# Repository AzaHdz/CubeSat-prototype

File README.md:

# CubeSat-prototype
Design, Build and test
###### STR: Structure, EPS: Electrical power Subsystem, CDH: Command data and handling, COM: Communications, ADC: Attitude Determination and Control, GCS: Ground Control Station
#### The purpose of this project is to develop the prototype of a CubeSat 1U type satellite, used in real space missions. 
#### 6 subsystems and a Ground control station were designed: EPS, Payload, CDH, COM, ADC, GCS and STR.
#### each subsystem was designed, built and tested
#### Communication protocols used: UART, I2C, Analog, SPI, Zigbee

#### The STR was designed in fusion 360 and built with  a 3d printer.

#### 5 pcb were designed in eagle and later they were manufactured in a chinese company

#### The two microcontrollers were programmed with the Arduino IDE.
#### The GUI was built with Node js and deployed as a web App.

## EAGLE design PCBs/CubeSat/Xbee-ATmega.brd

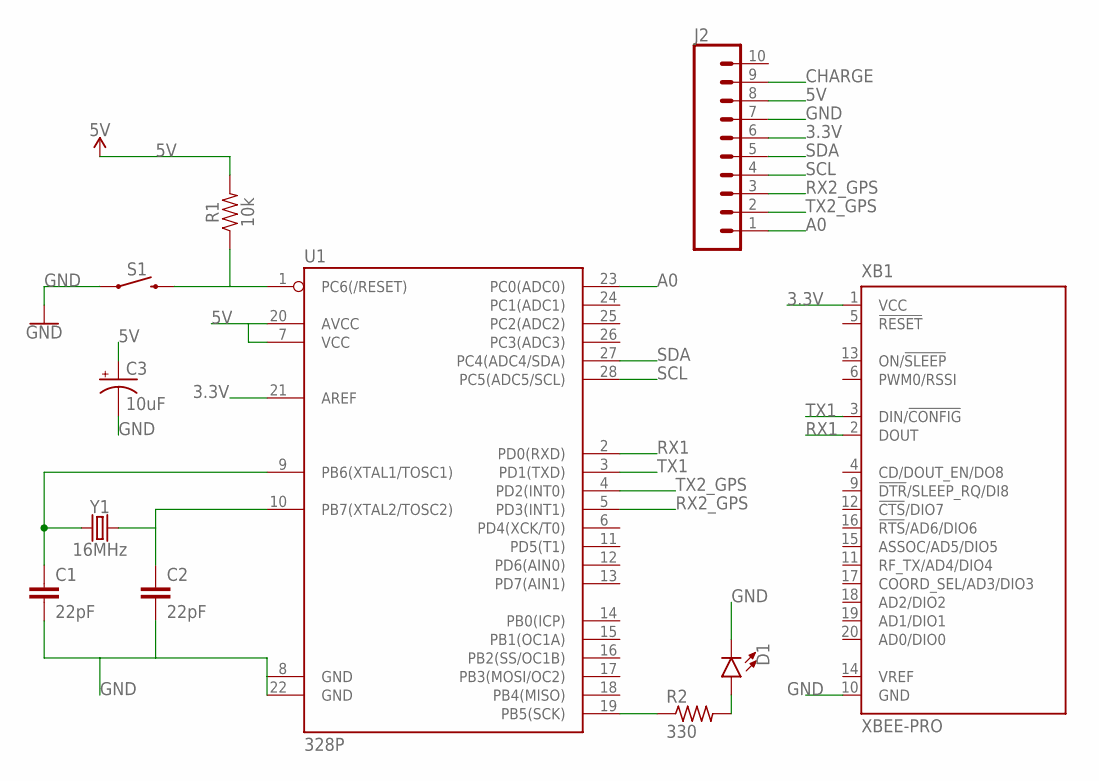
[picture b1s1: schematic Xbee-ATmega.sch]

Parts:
C1, C2: 22pF; CAP-PTH-2.54
C3: 10uF; CPOL-RADIAL-2.5MM-5MM
D1: LED5MM; LED_5MM
J2: CONN_10"; 1X10
R1: 10k; AXIAL-0.3
R2: 330; 0207/7
S1: MOMENTARY-SWITCH-SPST-PTH-6.0MM; TACTILE_SWITCH_PTH_6.0MM
U1: 328P; DIP28
XB1: XBEE-PRO
Y1: 16MHz; HC49US

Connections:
3.3V: J2.6, U1.21 (AREF), XB1.1 (VCC)
5V: C3.1 (+), J2.8, R1.P$2 (2), U1.7 (VCC), U1.20 (AVCC)
A0: J2.1, U1.23 (PC0(ADC0))
CHARGE: J2.9
GND: C1.2, C2.2, C3.2 (-), D1.K (C), J2.7, S1.1, U1.8 (GND), U1.22 (GND), XB1.10 (GND)
unnamed: R1.P$1 (1), S1.3 (2), U1.1 (PC6(/RESET))
unnamed: C2.1, U1.10 (PB7(XTAL2/TOSC2)), Y1.2
unnamed: C1.1, U1.9 (PB6(XTAL1/TOSC1)), Y1.1
unnamed: R2.1, U1.19 (PB5(SCK))
unnamed: D1.A, R2.2
RX1: U1.2 (PD0(RXD)), XB1.2 (DOUT)
RX2_GPS: J2.3, U1.5 (PD3(INT1))
SCL: J2.4, U1.28 (PC5(ADC5/SCL))
SDA: J2.5, U1.27 (PC4(ADC4/SDA))
TX1: U1.3 (PD1(TXD)), XB1.3 (DIN/!CONFIG)
TX2_GPS: J2.2, U1.4 (PD2(INT0))

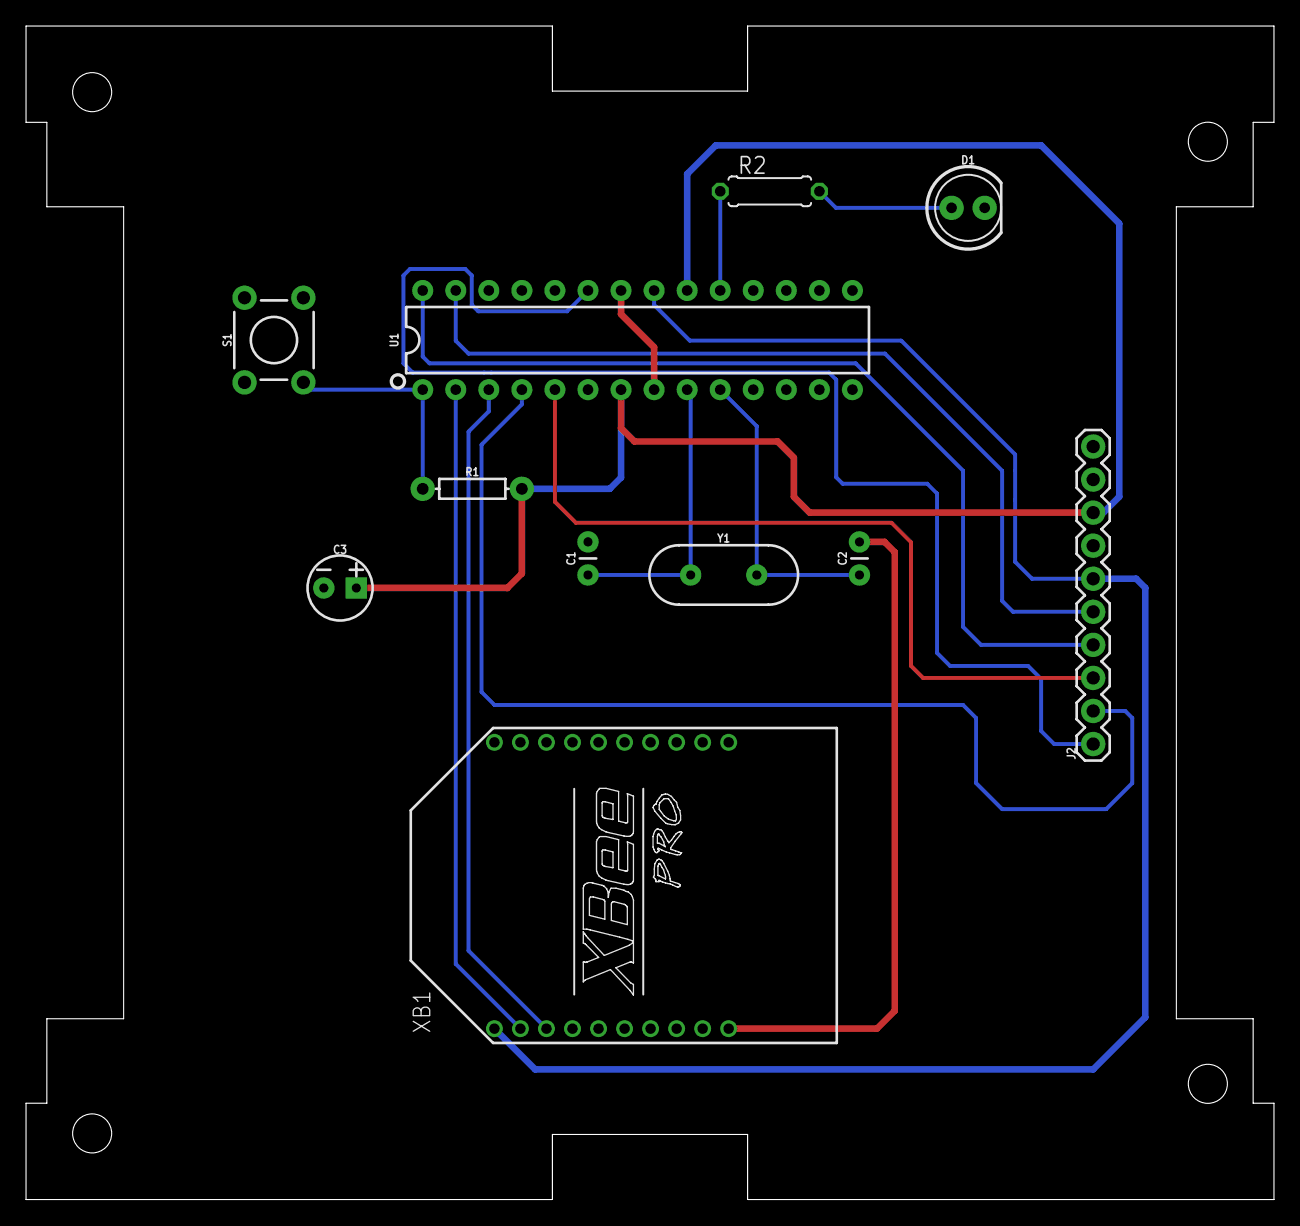
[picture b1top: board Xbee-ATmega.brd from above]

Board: 2 copper layers, 95.9 x 90.2 mm, 11 parts (0 on the bottom side), 15 nets.

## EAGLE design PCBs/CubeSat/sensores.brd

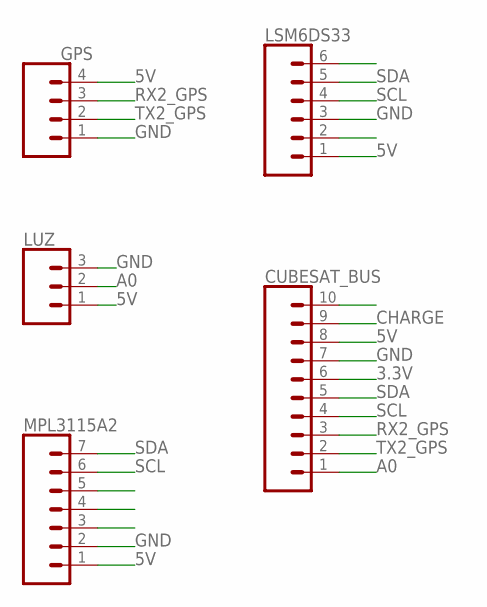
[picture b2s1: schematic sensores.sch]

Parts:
CUBESAT_BUS: CONN_10"; 1X10
GPS: CONN_04; 1X04
LSM6DS33: CONN_06SILK_FEMALE_PTH; 1X06
LUZ: CONN_03; 1X03
MPL3115A2: CONN_07; 1X07

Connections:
3.3V: CUBESAT_BUS.6
5V: CUBESAT_BUS.8, GPS.4, LSM6DS33.1, LUZ.1, MPL3115A2.1
A0: CUBESAT_BUS.1, LUZ.2
CHARGE: CUBESAT_BUS.9
GND: CUBESAT_BUS.7, GPS.1, LSM6DS33.3, LUZ.3, MPL3115A2.2
RX2_GPS: CUBESAT_BUS.3, GPS.3
SCL: CUBESAT_BUS.4, LSM6DS33.4, MPL3115A2.6
SDA: CUBESAT_BUS.5, LSM6DS33.5, MPL3115A2.7
TX2_GPS: CUBESAT_BUS.2, GPS.2

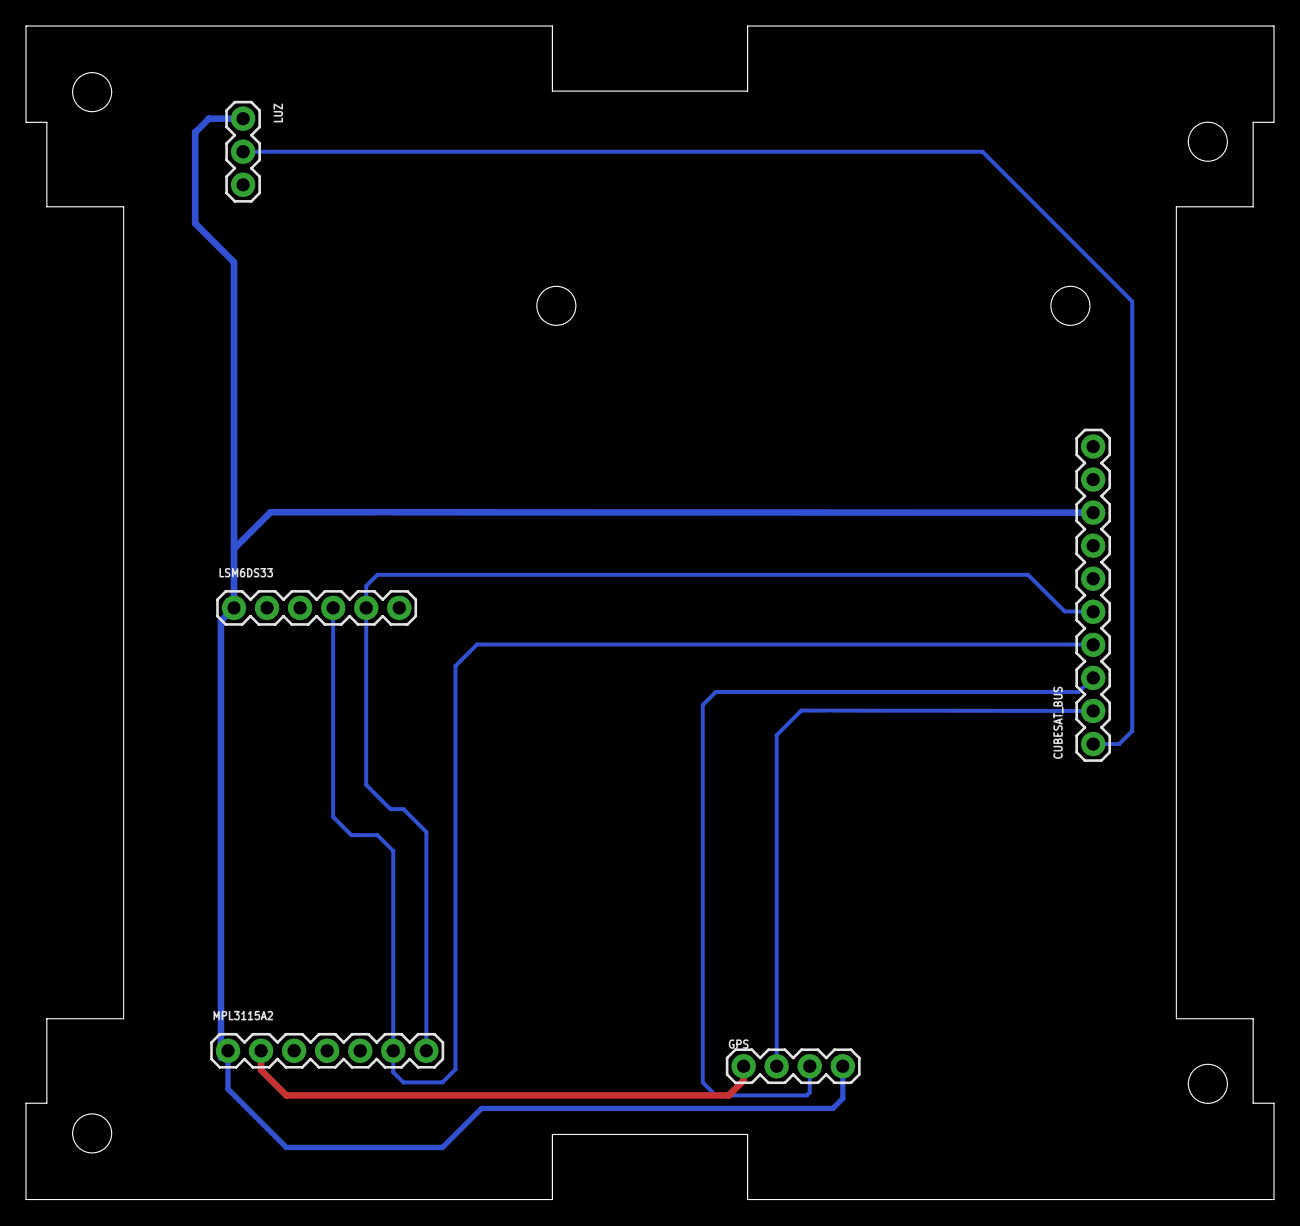
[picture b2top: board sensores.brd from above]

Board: 2 copper layers, 95.9 x 90.2 mm, 5 parts (0 on the bottom side), 7 nets.

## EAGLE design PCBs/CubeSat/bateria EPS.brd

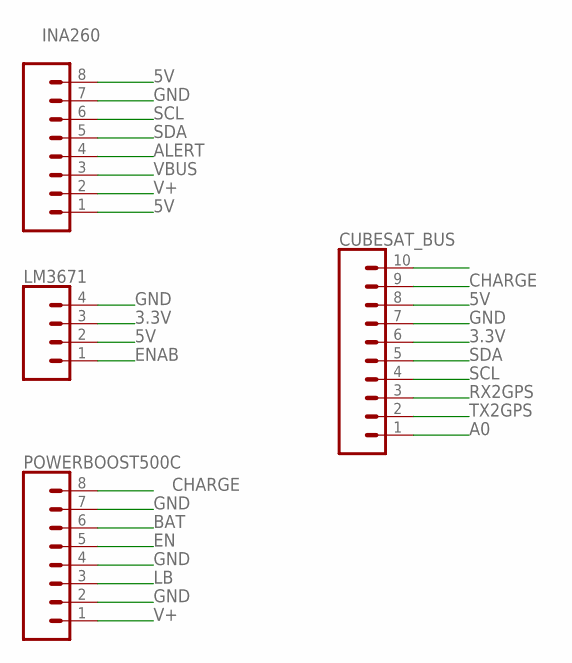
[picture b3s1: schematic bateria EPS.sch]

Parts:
CUBESAT_BUS: CONN_10"; 1X10
INA260: CONN_08"; 1X08
LM3671: CONN_04PTH; 1X04
POWERBOOST500C: CONN_08"; 1X08

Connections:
3.3V: CUBESAT_BUS.6, LM3671.3
5V: CUBESAT_BUS.8, INA260.1, INA260.8, LM3671.2
A0: CUBESAT_BUS.1
ALERT: INA260.4
BAT: POWERBOOST500C.6
CHARGE: CUBESAT_BUS.9, POWERBOOST500C.8
EN: POWERBOOST500C.5
ENAB: LM3671.1
GND: CUBESAT_BUS.7, INA260.7, LM3671.4, POWERBOOST500C.2, POWERBOOST500C.4, POWERBOOST500C.7
LB: POWERBOOST500C.3
RX2GPS: CUBESAT_BUS.3
SCL: CUBESAT_BUS.4, INA260.6
SDA: CUBESAT_BUS.5, INA260.5
TX2GPS: CUBESAT_BUS.2
V+: INA260.2, POWERBOOST500C.1
VBUS: INA260.3

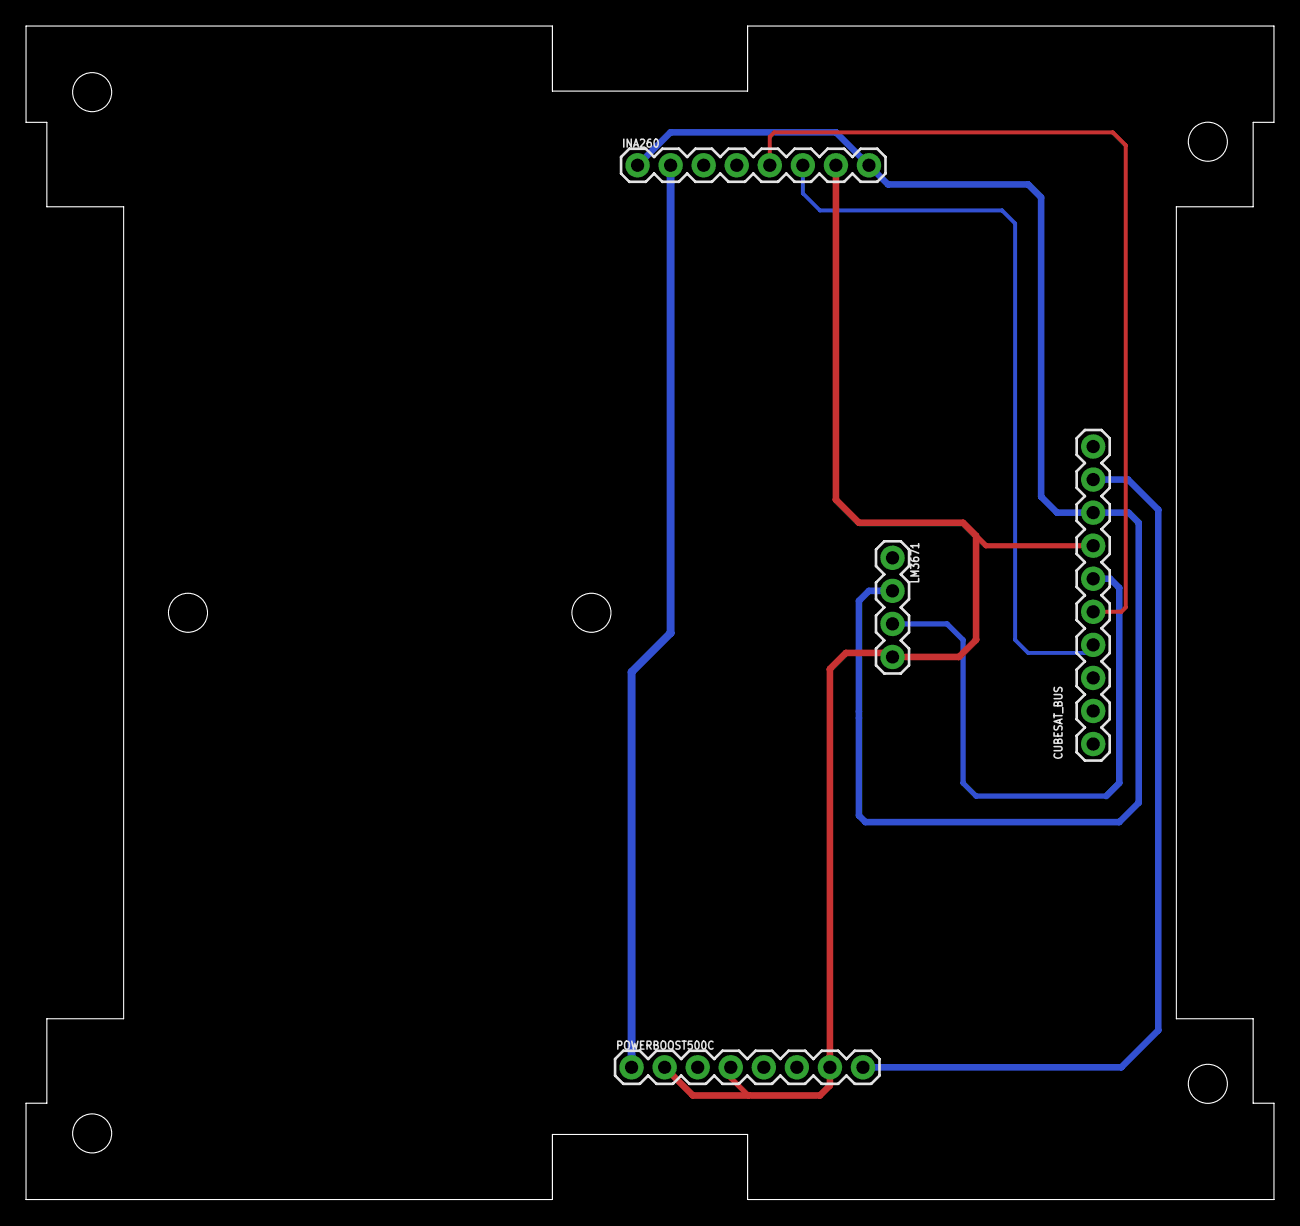
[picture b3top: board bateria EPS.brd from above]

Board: 2 copper layers, 95.9 x 90.2 mm, 4 parts (0 on the bottom side), 7 nets.

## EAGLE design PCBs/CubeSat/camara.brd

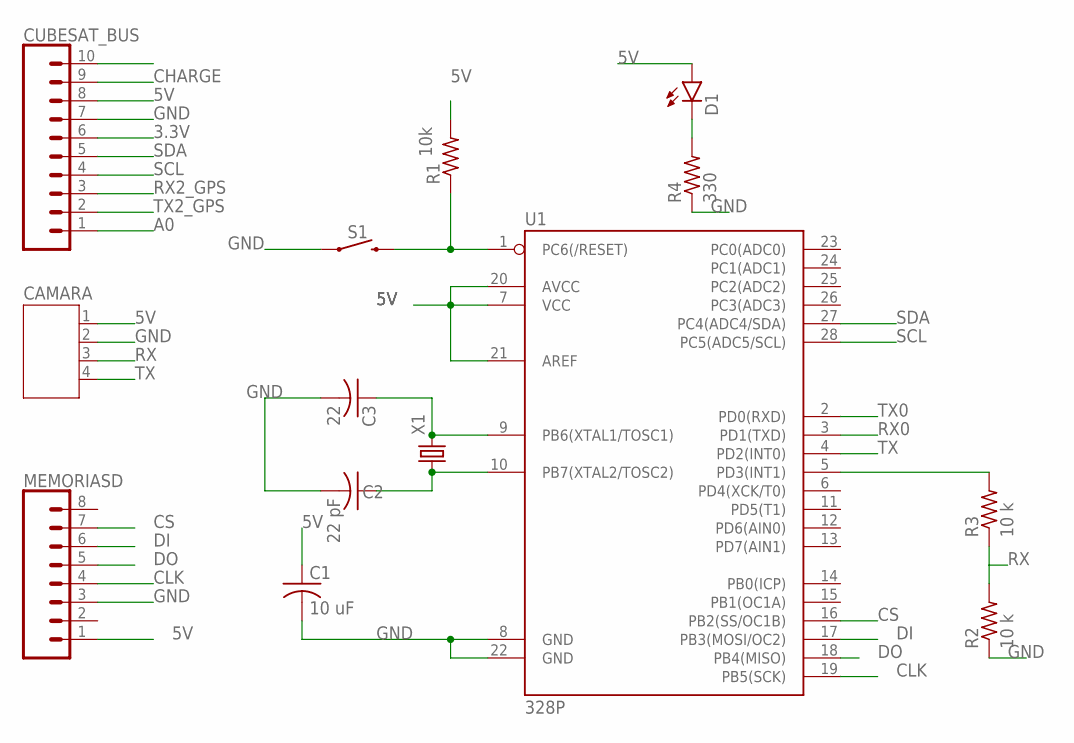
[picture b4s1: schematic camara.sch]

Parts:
C1: 10 uF; C025-025X050
C2: 22 pF; C025-025X050
C3: 22; C025-025X050
CAMARA: JST-PH4
CUBESAT_BUS: CONN_10"; 1X10
D1: BEAGLEBONE_BLUE_LED-3MM-NO_SILK; BEAGLEBONE_BLUE_BEAGLEBONE_BLUE_LED3MM-NS
MEMORIASD: CONN_08"; 1X08
R1: R-US_0204/7; 0204/7
R2, R3: 10 k; 0204/7
R4: 330; 0204/7
S1: MOMENTARY-SWITCH-SPST-PTH-6.0MM; TACTILE_SWITCH_PTH_6.0MM
U1: 328P; DIP28
X1: CRYSTALS-NOGND-HC49; HC49

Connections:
3.3V: CUBESAT_BUS.6
5V: C1.1, CAMARA.1, CUBESAT_BUS.8, D1.A, MEMORIASD.1, R1.2, U1.7 (VCC), U1.20 (AVCC), U1.21 (AREF)
A0: CUBESAT_BUS.1
CHARGE: CUBESAT_BUS.9
CLK: MEMORIASD.4, U1.19 (PB5(SCK))
CS: MEMORIASD.7, U1.16 (PB2(SS/OC1B))
DI: MEMORIASD.6, U1.17 (PB3(MOSI/OC2))
DO: MEMORIASD.5, U1.18 (PB4(MISO))
GND: C1.2, C2.2, C3.2, CAMARA.2, CUBESAT_BUS.7, MEMORIASD.3, R2.1, R4.1, S1.1, U1.8 (GND), U1.22 (GND)
unnamed: R1.1, S1.3 (2), U1.1 (PC6(/RESET))
unnamed: C3.1, U1.9 (PB6(XTAL1/TOSC1)), X1.2
unnamed: C2.1, U1.10 (PB7(XTAL2/TOSC2)), X1.1
unnamed: R3.2, U1.5 (PD3(INT1))
unnamed: D1.K (C), R4.2
RX: CAMARA.3, R2.2, R3.1
RX0: U1.3 (PD1(TXD))
RX2_GPS: CUBESAT_BUS.3
SCL: CUBESAT_BUS.4, U1.28 (PC5(ADC5/SCL))
SDA: CUBESAT_BUS.5, U1.27 (PC4(ADC4/SDA))
TX: CAMARA.4, U1.4 (PD2(INT0))
TX0: U1.2 (PD0(RXD))
TX2_GPS: CUBESAT_BUS.2

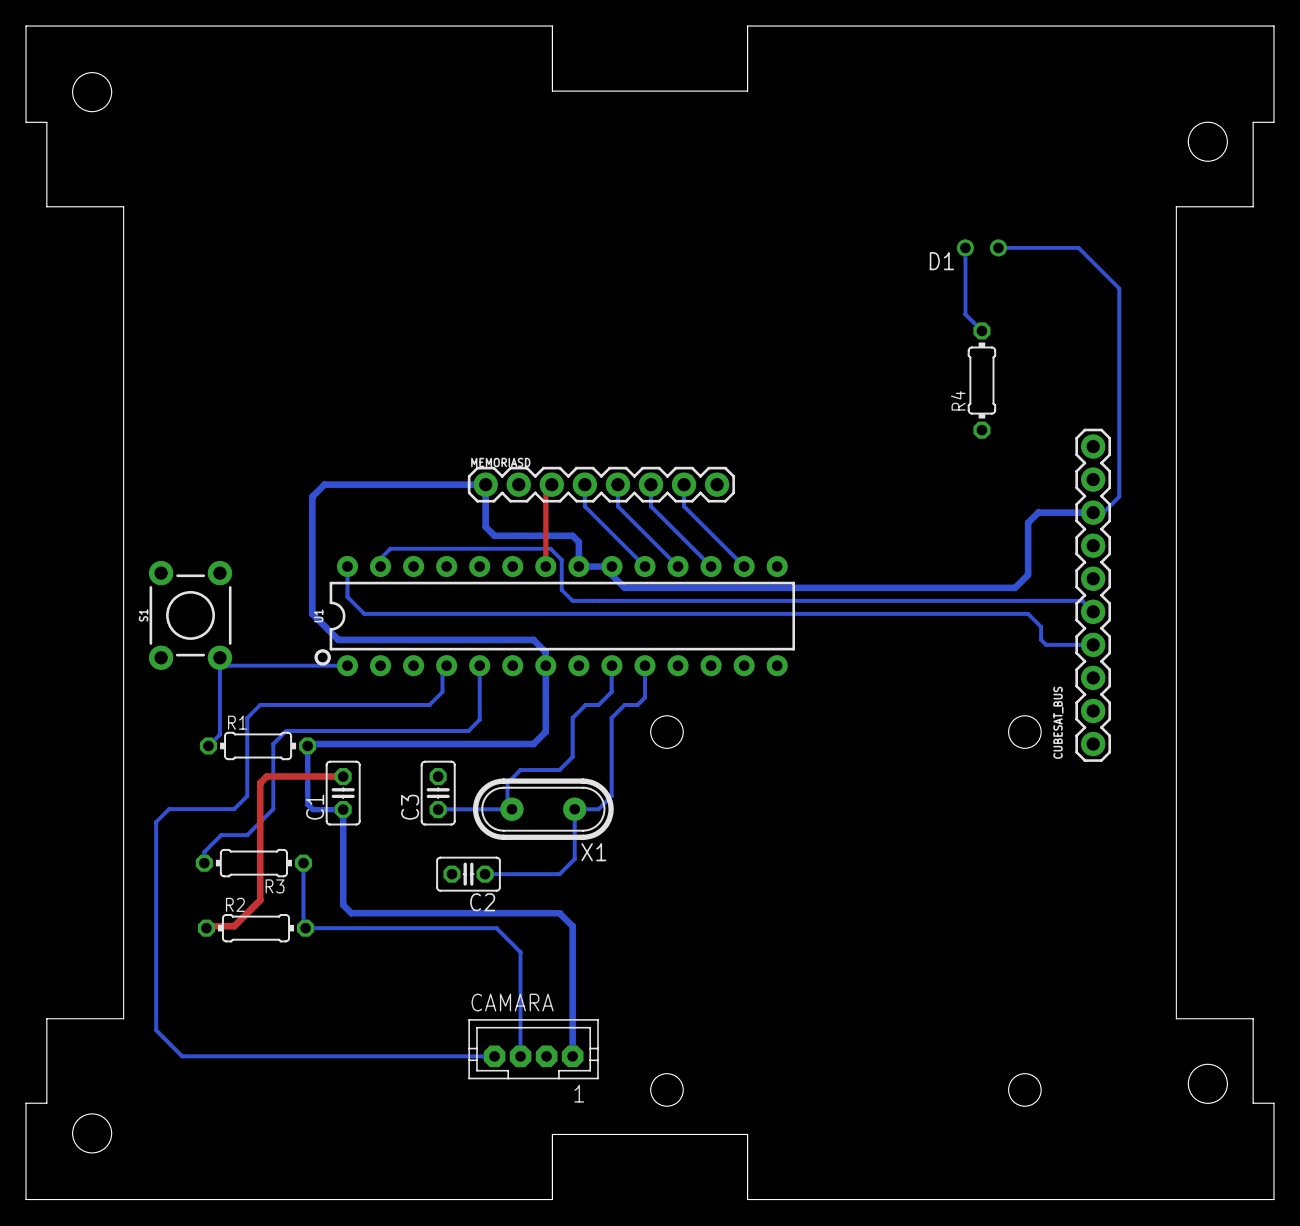
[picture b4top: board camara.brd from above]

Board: 2 copper layers, 95.9 x 90.2 mm, 14 parts (0 on the bottom side), 15 nets.

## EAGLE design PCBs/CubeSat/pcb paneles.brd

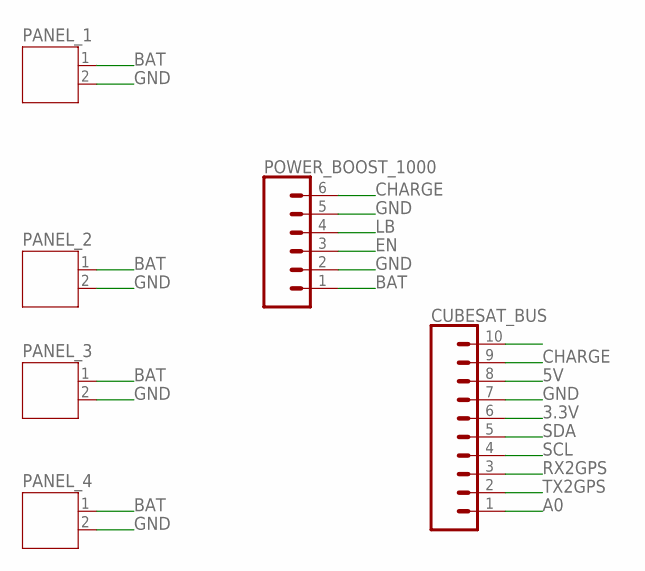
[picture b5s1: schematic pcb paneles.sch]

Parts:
CUBESAT_BUS: CONN_10"; 1X10
PANEL_1, PANEL_2, PANEL_3, PANEL_4: JST-PH2
POWER_BOOST_1000: CONN_06SILK_FEMALE_PTH; 1X06

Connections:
3.3V: CUBESAT_BUS.6
5V: CUBESAT_BUS.8
A0: CUBESAT_BUS.1
BAT: PANEL_1.1, PANEL_2.1, PANEL_3.1, PANEL_4.1, POWER_BOOST_1000.1
CHARGE: CUBESAT_BUS.9, POWER_BOOST_1000.6
EN: POWER_BOOST_1000.3
GND: CUBESAT_BUS.7, PANEL_1.2, PANEL_2.2, PANEL_3.2, PANEL_4.2, POWER_BOOST_1000.2, POWER_BOOST_1000.5
LB: POWER_BOOST_1000.4
RX2GPS: CUBESAT_BUS.3
SCL: CUBESAT_BUS.4
SDA: CUBESAT_BUS.5
TX2GPS: CUBESAT_BUS.2

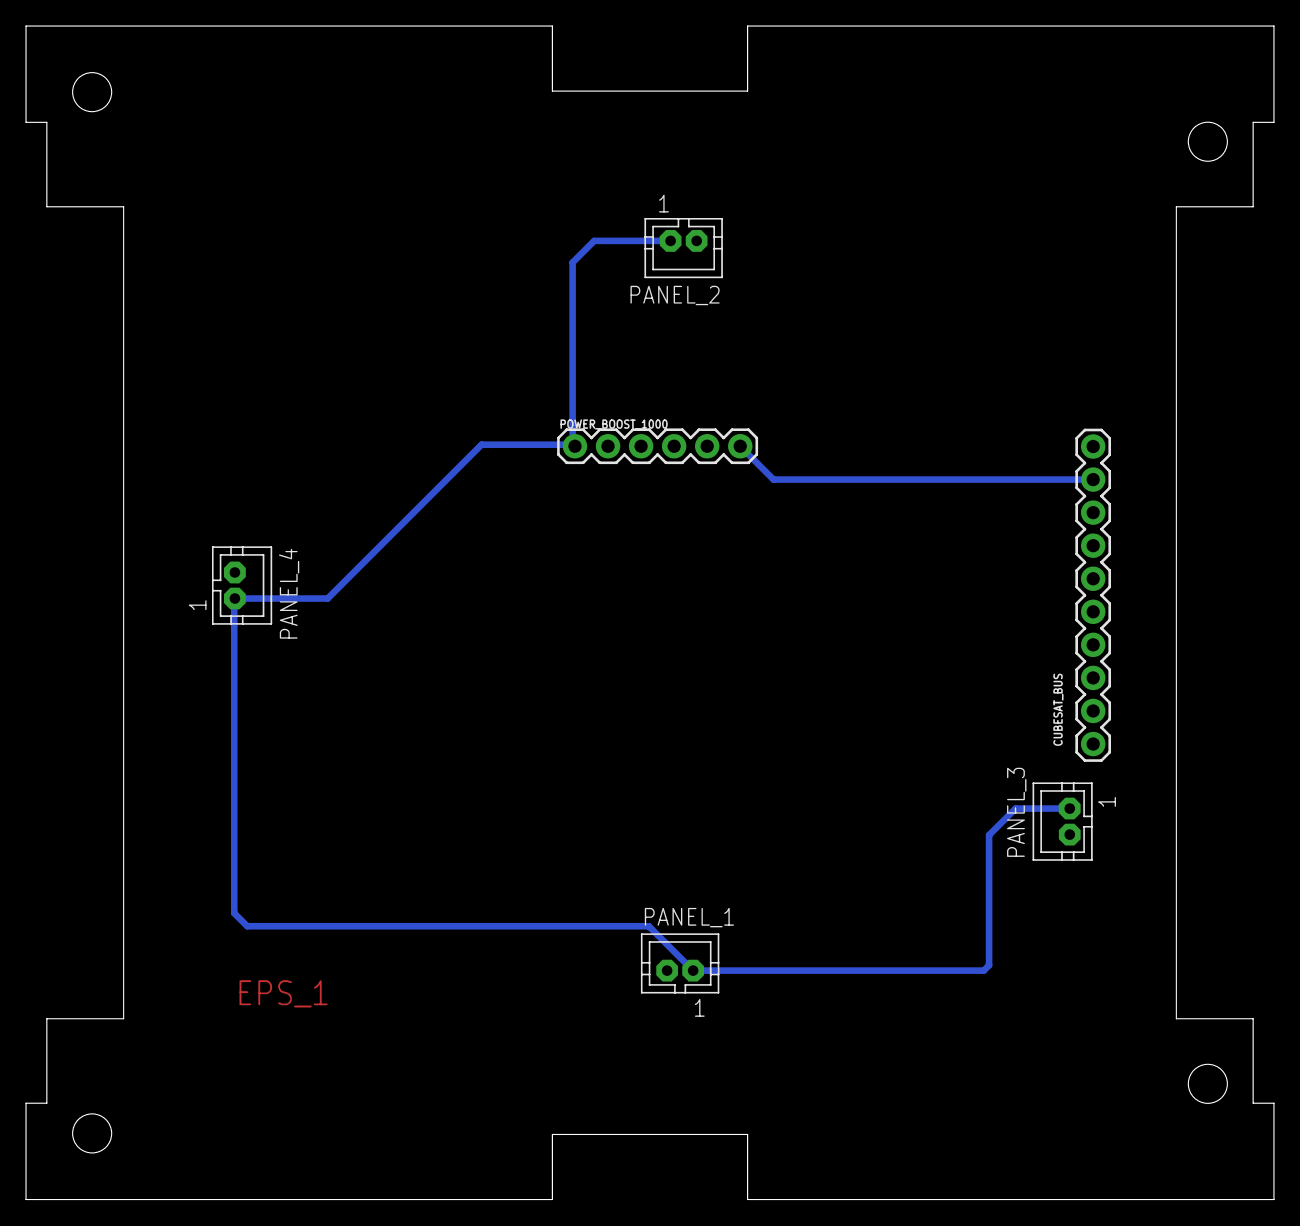
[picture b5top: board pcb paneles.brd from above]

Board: 2 copper layers, 95.9 x 90.2 mm, 6 parts (0 on the bottom side), 3 nets.

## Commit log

2020-11-06 add img
2020-11-06 Créate README

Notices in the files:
parts and their libraries:
SparkFun-Capacitors: Licensing: Creative Commons ShareAlike 4.0 International - https://creativecommons.org/licenses/by-sa/4.0
